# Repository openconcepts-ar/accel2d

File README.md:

# Hardware accelerated graphics (2D GPU) - graphics server system

## Introduction

This project aims to provide a graphics server system based on hardware accelerated graphics, and a easy way to develop the graphics primitives. The accelerated versions runs faster using the exact same C code as the software version by automatic translation (*transpiling*) to Verilog code.

As an example, let's see how to use and develop drawing privimites for solid rectangles and ellipses.

Ellipse case (see [ellipse_fill32.cc](./ellipse_fill32.cc) file):

    MODULE ellipse_fill32(
      bus_master(bus),
      const uint16&	x0,
      const uint16&	x1,
      const uint16&	y0,
      const uint16&	y1,
      const uint32&	rgba, //color
      const uint32& base, //pixel offset
      const int16& xstride, //normally 1, but can run backwards
      const int16& ystride //bytes to skip for next line (usually the framebuffer width * 4 bytes)
      )

The `bus` argument is automatically handled both in software and in hardware by privided macros.  
The rectangle primitive follows the same function signature.

## Software implementation

You can directly call the function using compilation with a normal C compiler:

    ellipse_fill32(BUSMASTER_ARG, x0, x1, y0, y1, rgba, base, xstride, ystride);

The BUSMASTER_ARG macro is an automatic argument, defined on a provided header file.
It's useful for the implementation of the hardware accelerated primitive, as explained in the next section.

The following image is produced by the simulator by calling 1000 times to the software implementation of the primitives,  using random coordinates:

</img>

## Hardware implementation

To target hardware implementation on a FPGA, a [Verilog](./ellipse_fill32.v) file is automatically generated from from the [corresponding C file](./ellipse_fill32.cc) having the drawing primitive algorithm, by using the following external tools: [CflexHDL](https://github.com/suarezvictor/CflexHDL) and the [Silice](https://github.com/sylefeb/Silice) transpilers (see [Makefile.common](./Makefile.common) target "c2v" for the invocation command details). Since this project aims to be transpiler-agnostic, the [PipelineC](https://github.com/JulianKemmerer/PipelineC) transpiler is planned for a future version.

See a portion of the generated Verilog code, where part of the C expressions and interactions with the memory bus can be readily appreciated:

    4: begin
        if (_q_x<_q_rw) begin
            _t_xx = _q_x*_q_x;
            _t_xh = (_t_xx)*(_q_hh);
            if (_t_xh+_q_yw<_q_wh) begin
                _d_bus_dat_w = in_rgba;
                _d_bus_we = 1;
                _d_bus_stb = 1;
                _d_bus_cyc = 1;
                if (!((_d_bus_stb&&_d_bus_we)&&!(_d_bus_stb&&in_bus_ack&&_d_bus_we))) begin
                    _d_bus_stb = 0;
                    _d_bus_adr = (_q_bus_adr+(in_xstride));
                    _d_x = _q_x+1;
                end
            end else begin
                _d_bus_adr = (_q_bus_adr+(in_xstride));
                _d_x = _q_x+1;
            end
            _d__idx_fsm0 = 4;
        end else begin
            _d__idx_fsm0 = 5;
        end
    end

After generating a System On Chip (SoC) for the target FPGA using the [LiteX](https://github.com/enjoy-digital/litex) framework and a [provided](./digilent_arty.py) script, that includes the generated verilog files, the accelerator can be called as follows:

    regs->x0 = x0;
    regs->x1 = x1;
    regs->y0 = y0;
    regs->y1 = y1;
    regs->base = VIDEO_FRAMEBUFFER_BASE + y0*FRAME_PITCH + x0*sizeof(rgba);
    regs->xstride = SDRAM_BUS_BITS/8;
    regs->ystride = FRAME_PITCH;
    regs->rgba = rgba;

    regs->run = 1; //start
    while(!regs->done); //wait until done

As seen, you first set memory mapped registers with the desired values, then you start the core, then wait until the `done` flag is set.

Each accelerator core gets mapped starting at a fixed address (default 0x80000000 for the first accelerator, 0x80000800 for the second and so on, as provided by the correspoding macros). A C structure with the layout of registers is conveniently provided too (each register is 32-bit aligned, even if smaller).

The resulting execution in hardware is as follows:

</img>

## Testing equivalence of software and hardware

You can visually appreciate that both images seems like the same, but how we can be sure the generated Verilog behaves the same as the software implementation? The solution is to use the accelerated implementations and also call the compiled software implementation in the same SoC, then we can compare if results are the same. The [test program](./drawing_test.c) does specifically that, reporting how many pixels are in error, if any:

You can see that the accelerator is about **3X faster**, while it also frees the CPU for other tasks.

In case of any discrepance, non-matching pixels are marked in red (this was generated by inducing a coordinate error in the software implementation) and the amount of pixels in error is reported.

Console output would be in this case:  
  
    Pixel errors: 320 (screen should have no red pixels)

    ==========================================
    *** TESTS FAILED ***
    ==========================================

## Prototype application and simulator

The acceleration is readily appreciated on the following [video](https://peertube.io/w/8ds2de9pjt3c6C22reAnZc), where the software implementation is run prior to the hardware one. After that, a *clock demo* application is shown, using a combination of drawn rectangles and ellipses.

</img>

The [code](./drawing_test.c) for that demo application can be compiled with the main [simulator](./sim_linux.c) code on the host machine (e.g. Linux) to see results on the simulator window. This eases testing while in development since the program compiles in few seconds, then it can be run on the hardware platform to check if producing the same results. In the provided video, you can see that the hardware matches the simulator.

## Accelerator performance

Accelerator cores gets directly connected to the dynamic RAM of the respective boards (acting similarly as a DMA), and using caching to achieve access at high speed. That way, the accelerated cores are about 7X faster than when running in software, as the current tests reports (line drawing core on a ECP5 device):

</img>

    Start software rendering
    elapsed 9057225 us, ops/s: 828153 (2 FPS @640x480)
    Switch to hardware rendering
    elapsed 1229585 us, ops/s: 6100246 (19 FPS @640x480)
    Just waiting a bit to evaluate image...
    Pixel errors: 0 (screen should have no red pixels)
    
    ==========================================
    TESTS PASSED
    ==========================================

The following [video](https://peertube.io/w/5h4g7QTLPuHQ6vtsUj8WzR) shows the corresponding images on the display (first the software renderer, then the accelerated renderer).

## Supported boards

Curently the project supports the following boards:  
[Lambdaconcept ECPIX-5](https://shop.lambdaconcept.com/home/46-ecpix-5.html) with a Lattice ECP5 device. It currently utilices an open source toolchain for building the bitstream. The board name used in the project is *lambdaconcept_ecpix5*.

[Digilent Arty A7-35T](https://digilent.com/reference/programmable-logic/arty-a7/) with an AMD Artix7 device. The board name used in the project is *digileny_arty*.

# Build instructions

Just run:

    make BOARD=lambdaconcept_ecpix5 run upload

Where the target *run* runs the simulator, and the *upload* target makes the bitstream and uploads it to the FPGA board.

# Micropython support, with graphics
The FPGA board is now capable of running a graphics-enabled micropython port, capable of controlling a PC monitor.
Up to 8 bit per color channel are supported.
  
Example: [accel_basic.py](./demos/micropython/accel_basic.py)  
  
</img>

## Build & run instructions for micropython:
Generate and upload the bitstream (use your own serial port location if different):

    make BOARD=digilent_arty digilent_arty SERIAL_PORT=/dev/ttyUSB1
    cd micropython/ports/litex
    make
    litex_term.py --kernel build/firmware.bin /dev/ttyUSB1
    cd -
    openFPGALoader -b arty build/digilent_arty/gateware/digilent_arty.bit

Then the .py file can be uploaded using the standard `mpremote` command:

    mpremote connect /dev/ttyUSB1 run demos/micropython/accel_basic.py

This generates the following picture:  
  
</img>

To run the clock demo, [accel_clock.py](./demos/micropython/accel_clock.py)  (in same folder)

## Micropython support on the CPU board
  
The same repository used for the port of micropython to the FPGA platform was used to target the project's CPU board (F133A SoC by Allwinner Tech)

Supported features are:  
  * REPL (Python prompt) over UART  
  * Minimal umachine support  
  * Time functions (except RTC)  
  * Video Framebuffer
  * Dynamic memory allocation (using the internal DDR2 RAM)

The repository of the extended micropython is linked as a git submodule on the main repo (see [micropython@51dfc37b30](https://notabug.org/suarezvictor/gpu2d) at the project's main repo). The sub repository directs to the micropython [repo](https://github.com/suarezvictor/micropython/tree/gpu2d).

The source for the f133 port are under the following [folder](https://github.com/suarezvictor/micropython/tree/gpu2d/ports/f133)
  
A basic example to test micropython on the CPU is to use the REPL mode:
  
</img>

Under the f133 folder, there's a micropython script that shows how to access the video framebuffer: [test/test_video.py](https://github.com/suarezvictor/micropython/blob/gpu2d/ports/f133/test/test_video.py)
  
</img>

Execution of this produced the following result:
  
</img>

Note the compatibility of the micropython code with the one for the [FPGA platform](https://github.com/suarezvictor/micropython/blob/gpu2d/ports/litex/test/test_video.py).

## Build instructions:  
```
cd ports/f133
make
```
The `make` command will build the firmware and upload it to the board. To upload new firmware, you have to first push the reset button.

# New CPU-based board
A brand-new board was designed using a graphics-capable CPU:

</img>

It's capable of running the [clock demo](./target-cpu/drawing_test.c), using the graphics primitives [ellipse](./ellipse_fill32.cc) and [rectangle fill](./rectangle_fill32.cc)

This produces the following image:  
</img>

## Build instructions:  
```
   cd target-cpu/f133-bare/
   make
```

The `make` command will build the firmware and upload it to the board. To upload new firmware, you have to first push the reset button.

This milestone is **conclusive proof** that this framework is capable running the drawing primitives as software or hardware, since the same code runs on the CPU as software and in the FPGA as a hardware core, producing matching visual results.

The same port of micropython to the FPGA platform was used to target the project's CPU board (F133A SoC by Allwinner Tech)

# Serial communications

The CPU board is capable of communication using serial ports, they're typically used to control the board externally and to get debug messages.

See an example of boot mesages outputted from the default debug port (UART0):
  
</img>

See below an example interaction with micropython using the second port (UART1), accesible in the board at the 6-pin header (bottom left).
  
</img>

This is achieved in software by calling a initialization function `uart_probe(UART_COMM)` to enable the second port. See [main.c](target-cpu/f133-bare/main.c) for a example usage and [driver_uart.c](target-cpu/f133-bare/driver_uart.c) for the implementation.

## I2C
An I2C driver was added to the micropython port for the CPU board. It can access display information provided by PC monitors and determine available resolutions.

It works by configuring I/O pins for open-drain behaviour, thus electrically compatible with the I2C standard.
See [mphalport.h](https://github.com/suarezvictor/micropython/blob/1be3d4751f3e6832b87b66c13be2fca8f1f1078a/ports/f133/mphalport.h#L64) for implementation details.

The micropython script to run is: [i2c_vga_ddc.py](demos/micropython/i2c_vga_ddc.py), which obtains the following information:
  
</img>

The script can be run from the Linux console with the `mpremote` command:
```
mpremote connect /dev/ttyUSB0 run demos/micropython/i2c_vga_ddc.py
```

The wiring can be done using the [I/O board](hardware/IO_board) using a 40-pin FPC cable and direct wiring to the VGA connector as shown:   
</img>

# Software JPEG image decompression

A new function to decompress JPEG file was implemented, it's based on the C model of a [Verilog decompressor](https://github.com/ultraembedded/core_jpeg), so in that form it's useful to test things in sofware before moving it to hardware. The original code was changed to avoid dynamic memory allocations thus easier to run in the bare metal environment, see [target-cpu/f133-bare](target-cpu/f133-bare) for sources.

A JPEG file is embedded in the firmware image by means of a direct include of the raw file data (.incbin directive in the [rawdata.S](target-cpu/f133-bare/rawdata.S) assembler source)

The example image size is 33.8KB when compressed and 921.6 KB when decompressed (27:1 ratio). Software decompresion takes 195ms (5FPS) expected to reach 30FPS with the planned video decoder accelerator (Verilog).

Working example on the bare metal enviroment:
  
</img>

The decompression algorithm is in the [c_model_jpeg_test.cpp](target-cpu/f133-bare/c_model_jpeg_test.cpp) source.

# About [NLnet](http://nlnet.nl) Foundation

</img>

This [project](https://nlnet.nl/project/Hardware-2D) is funded through the NGI0 Entrust Fund, a fund established by NLnet with financial support from the European Commission's Next Generation Internet programme, under the aegis of DG Communications Networks, Content and Technology under grant agreement No 101069594.

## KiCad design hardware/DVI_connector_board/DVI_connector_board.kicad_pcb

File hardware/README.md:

# HARDWARE (boards)

Here are the design files for the current boards of this project:  

Processing boards:  
  * [CPU board](#cpu-board-design) [_viewer_](https://kicanvas.org/?repo=https%3A%2F%2Fgithub.com%2Fopenconcepts-ar%2Faccel2d%2Ftree%2Fpcbfixes1%2Fhardware%2FCPU_board)  
  * [ECP5 FPGA board](#ECP5-fpga-board-design) [_viewer_](https://kicanvas.org/?repo=https%3A%2F%2Fgithub.com%2Fopenconcepts-ar%2Faccel2d%2Ftree%2Fpcbfixes1%2Fhardware%2FFPGA_board)  
  * [Spartan-6 FPGA board](#spartan-6-fpga-board) [_viewer_](https://kicanvas.org/?repo=https%3A%2F%2Fgithub.com%2Fopenconcepts-ar%2Faccel2d%2Ftree%2Fpcbfixes1%2Fhardware%2FSpartan6_board)  

Adapter boards:  
  * [eDP adapter board](#edp-adapter-design) [_viewer_](https://kicanvas.org/?repo=https%3A%2F%2Fgithub.com%2Fopenconcepts-ar%2Faccel2d%2Ftree%2Fpcbfixes1%2Fhardware%2FeDP_adapter)  
  * [eDP adapter board, alternate IC version](#edp-adapter-design) [_viewer_](https://kicanvas.org/?repo=https%3A%2F%2Fgithub.com%2Fopenconcepts-ar%2Faccel2d%2Ftree%2Fpcbfixes1%2Fhardware%2FeDP_adapter%2Fedp_adapterITE)  
  * [VGA adapter](#vga-adapter-board-design) & connector [_viewer_](https://kicanvas.org/?repo=https%3A%2F%2Fgithub.com%2Fopenconcepts-ar%2Faccel2d%2Ftree%2Fpcbfixes1%2Fhardware%2FVGA_adapter)  
  * [LVDS adapters](#lvds-adapter-board-design) single and dual channel [_viewer_](https://kicanvas.org/?repo=https%3A%2F%2Fgithub.com%2Fopenconcepts-ar%2Faccel2d%2Ftree%2Fpcbfixes1%2Fhardware%2FLVDS_adapter)  
  * [DVI adapter](#dvi-adapter-board-design) & connector [_viewer_](https://kicanvas.org/?repo=https%3A%2F%2Fgithub.com%2Fopenconcepts-ar%2Faccel2d%2Ftree%2Fpcbfixes1%2Fhardware%2FDVI_adapter)  
  * [DVI passive adapter](#dvi-passive-adapter-board-design) [_viewer_](https://kicanvas.org/?repo=https%3A%2F%2Fgithub.com%2Fopenconcepts-ar%2Faccel2d%2Ftree%2Fpcbfixes1%2Fhardware%2FDVI_connector_board)  
  * [USB to I2C bridge](#usb-to-i2c-bridge) [_viewer_ NOTE: select USBHOST project](https://kicanvas.org/?repo=https%3A%2F%2Fgithub.com%2Fopenconcepts-ar%2Faccel2d%2Ftree%2Fpcbfixes1%2Fhardware%2FTouch_splitter)   

Debugging boards:  
  * [DVI receiver](#dvi-receiver-board) [_viewer_](https://kicanvas.org/?repo=https%3A%2F%2Fgithub.com%2Fopenconcepts-ar%2Faccel2d%2Ftree%2Fpcbfixes1%2Fhardware%2FDVI_receiver)  
  * [Touch splitter](#touch-splitter-board) [_viewer_](https://kicanvas.org/?repo=https%3A%2F%2Fgithub.com%2Fopenconcepts-ar%2Faccel2d%2Ftree%2Fpcbfixes1%2Fhardware%2FTouch_splitter)  
  * [I/O board](#io-board-design) [_viewer_](https://kicanvas.org/?repo=https%3A%2F%2Fgithub.com%2Fopenconcepts-ar%2Faccel2d%2Ftree%2Fpcbfixes1%2Fhardware%2FIO_board)  

## CPU board design
A second, smaller version of the CPU board was designed, based again on the Allwinner F133A CPU  
  
It features:  
  * C906 64-bit RISC-V CPU @1GHz (22nm manufacturing process)  
  * Integrated 64MB DDR2 RAM  
  * Small size, breadboard compatible  
  * SD card socket to store media assets  
  * 2 USB-C connectors with Host and OTG (Host/Device) functions, respectively  
  * Video output connector  
  * Headers for serial I/O and power  
  * Reset and boot buttons
  * JTAG debugging using "pogo-pins"  

The design is done with the open-source EDA tool [Kicad](https://kicad.org), the source files are [here](./CPU_board)  
The board is 4 layer, based on the [Yuzuki design](https://bbs.aw-ol.com/topic/922/%E5%BC%80%E6%BA%90-yuzukinezha-d1s-%E6%A0%B8%E5%BF%83%E6%9D%BF-mini-pice-%E6%A0%B8%E5%BF%83%E6%9D%BF/3), with **CERN open-source hardware** license.
  
PDF schematics are [here](./CPU_board/CPU_board_schematics.pdf).  

## ECP5 FPGA board design

The ECP5 FPGA board is capable of instancing a RISC-V CPU along with the hardware accelerators desiged in C and automatically translated to Verilog.
Not only the board has the same layout as the CPU board but the drawing primitives use the same C sources, as one of the main objectives of the project.

Features are:  
  * Lattice ECP5 FPGA device, supporting 12F, 25F, 45F and 85F sizes in 285 ball BGA package  
  * DDR3L RAM of up to 1Gbit with impedance controlled tracks  
  * Small size, breadboard compatible  
  * SD card socket to store media assets  
  * 2 USB-C connectors with Host and Device functions, respectively  
  * Video output connector  
  * Headers for serial I/O  
  * Reset button (also for bitstream loading)
  * JTAG debugging using "pogo-pins"  

The design is done with the open-source EDA tool [Kicad](https://kicad.org), the source files are [here](./FPGA_board)  
The board is 6 layer, based on the [OrangeCrab board r0.1](https://orangecrab-fpga.github.io/orangecrab-hardware/docs/r0.1/), with **CERN open-source hardware** license.
  
PDF schematics are [here](./FPGA_board/FPGA_board_schematics.pdf).  

*NOTE: FPGA chip is not shown on the 3D rendering for lack of a 3D model for the part*

## Spartan-6 FPGA board

The Spartan-6 FPGA board is a lower cost version FPGA board. It includes a DDR3 memory and a RP2040 MCU. I/O includes a flash memory connector, USB-C device port, a 20-pin FPC connector for DVI (TDMS) signals, and a SWD debug header.  

The design is done with the open-source EDA tool [Kicad](https://kicad.org), the source files are [here](./Spartan6_board)  
The board is 6 layer, based on the [Modos Glider Lite](https://github.com/Modos-Labs/Glider/tree/df32bba2b8f32c97958a599ba021d12184ffeada/pcb/mainboard_lite), with **CERN open-source hardware** license.
  
PDF schematics are [here](./Spartan6_board/pcb.pdf).  

## eDP adapter design

This adapter is capable of converting <s>digital RGB parallel signals NOTE: lack of docs prevents this, see eDP_adapter/EDP.md</s> LVDS signals to eDP protocol for direct driving of laptop replacement displays using a standard FPC cable. The converter IC is NCS8801S from [NewCoSemi](https://www.newcosemi.com/), or IT6251 from [ITE](https://www.ite.com.tw/en) as an alternative. Note they are 4-layer design for better signal integrity, as required by the high-speed differential LVDS inputs and eDP outputs.

The design source files are [here](./eDP_adapter).  
PDF schematics for the adapter are [here](./eDP_adapter/eDP_adapter.pdf).  

**Alternate version**:  

The design source files are [here](./eDP_adapter).  

Thiese designs are relased under a **CERN open-source hardware** license, using the the open-source EDA tool [Kicad](https://kicad.org)

## VGA adapter board design

This adapter is capable of converting digital RGB parallel signals to VGA-compatible analog values, using a simple R-2R DAC. The adapter board outputs the VGA signals to a 15-pin flat cable, to be connected 1:1 to a connector board that has the D-sub (15-pin) starndard VGA connector.

The design is done with the open-source EDA tool [Kicad](https://kicad.org), the source files are [here](./VGA_adapter) (adapter) and [here](./VGA_connector_board) (connector)  
PDF schematics for the adapter are [here](./VGA_adapter/VGA_adapter_schematics.pdf).  
  
This design is relased under a **CERN open-source hardware** license.

## LVDS adapter board design

This board connects 4 or 8 pairs of differential signals to a LCD using LVDS signalling (of the kind commonly used for older laptops displays), to directly drive them (single and dual channel). It also connect signals that can identify the display model and resolution using I2C.

Features:  
  * 40-pin FPC cable connector  
  * Protection diodes  
  * I2C connection for display [EDID](https://en.wikipedia.org/wiki/Extended_Display_Identification_Data) reading  
  * External header for powering the backlight  

The design is done with the open-source EDA tool [Kicad](https://kicad.org), the source files are [here](./LVDS_adapter), licensed under a **CERN open-source hardware** license.  
  
PDF schematics for the adapter are [here](./LVDS_adapter/LVDS_adapter_schematics.pdf) (single channel) and [here](./LVDS_adapter/LVDS_adapter_2ch.pdf) (dual channel).  

**Dual channel**

**Single channel**

**8-bit dual channel**

This boards outputs a standard 2x15 2mm pitch LVDS connector on the side, supporting 1 or 2 channel, 6- or 8-bit versions. It adds a 6-pin I2C connector on the back for touch signals.  

## DVI adapter board design

This board converts parallel RGB signals to digital video signals in the DVI format, as accepted by the majority of current PC monitors and TVs.

Features:  
  * 20-pin FPC cable connector, compatible with standard [FPV Ribbon cables](https://duckduckgo.com/?hps=1&q=FPV+HDMI+Ribbon+Cable) for connection to displays  
  * Protection diodes  
  * I2C connection for display [EDID](https://en.wikipedia.org/wiki/Extended_Display_Identification_Data) reading  
  * Solder jumpers for the main IC configuration  

The design is done with the open-source EDA tool [Kicad](https://kicad.org), the source files are [here](./DVI_adapter) (adapter) and [here](./DVI_connector_board) (connector), licensed under a **CERN open-source hardware** license.  
  
PDF schematics for the adapter are [here](./DVI_adapter/DVI_adapter_schematics.pdf).  

**Connector board**
  
This was fixed for better signal integrity using a G-S-S-G scheme for the differential signals, using a pinout that is common in off-the-shelf extension adapters.   

## DVI passive adapter board design

This is for outputting LVDS signals from a FPGA using AC-coupling to drive a TDMS receiver, using a standard connector for carring DVI video signals.
It includes a level adapter to convert 5V I2C to 3.3V (VIO).

The design is done with the open-source EDA tool [Kicad](https://kicad.org), the source files are [here](./LVDS_DVI_adapter), licensed under a **CERN open-source hardware** license.  
  
PDF schematics for the adapter are [here](./LVDS_DVI_adapter/LVDS_DVI_adapter.pdf).  

## DVI receiver board

This board converts DVI (TDMS) signals to parallel RGB signals + H/V sync. It is based on the TFP401 chip from TI.

The design is done with the open-source EDA tool [Kicad](https://kicad.org), the source files are [here](./DVI_adapter) (adapter) and [here](./DVI_connector_board) (connector), licensed under a **CERN open-source hardware** license.  
  
PDF schematics for the adapter are [here](./DVI_adapter/DVI_adapter_schematics.pdf).  

## Touch splitter board

The touch splitter board allows to split the signals from a 40-pin eDP display woth on-cell touch, separating the 30-pin eDP signals and the USB touch signals. It supports powering the touch model with 5V or 3.3V.

The design is done with the open-source EDA tool [Kicad](https://kicad.org), the source files are [here](./Touch_splitter). 

## USB to I2C Bridge
This board is a 40-pin extended eDP with touch to 30-pin with bridged I2C. It is similar top the Touch splitter board, but "active": instead of passively exposing the USB signals to an external connector, it routes them to a MCU.
  
The board uses a RP2354 as the MCU wich supports USB full-speeed host (unsing the USB signals on the connector with the additional 10 pins) and outputs I2C data over a usual 30-pin eDP connector. It uses "OEM reserved" pins to route the I2C signals and the interrupt pin. This is received by the eDP adapter which supports touch-enabled display reusing it's 30-pin output FPC connector, being still compatible with non-touch enabled 30-pin displays.

The design is done with the open-source EDA tool [Kicad](https://kicad.org), the source files are [here](./Touch_splitter), see `eDP_touch_adapter_USBHOST.kicad_*` files. 

## I/O board design

The I/O board adapter allows to externally access the video signals (present on the 2x15 connectors) for other purposes like general purpose I/O pins and debug.

It uses a 40-pin FPC connector and cable that allows to break out the signals, in a more manageable way like using common wires as the ones usually for bread boards.

Also, it includes two 31-pin FPC connectors at 0.3mm pitch for replacing the Hirose connectors with FPC or FFCs.
All the wiring are directo connections to the video connectors. A header to acces the touchscreen signal is also provided.

The design is done with the open-source EDA tool [Kicad](https://kicad.org), the source files are [here](./IO_board), licensed under a **CERN open-source hardware** license.  

# Latest updates

See most relevant [commit](https://github.com/openconcepts-ar/accel2d/commit/21333764fecb12ceccd276d67593bb1683f1b8bd).  

  * Added [eDP adapter board](#edp-adapter-design), alternate version
  * Added [USB to I2C bridge](#usb-to-i2c-bridge)
  * Added [LVDS adapters, 8-bit version dual channel](#lvds-adapter-board-design)
  * Updated [eDP adapter board](#edp-adapter-design) to 4 layers
  * Added [Spartan-6 FPGA board](#spartan-6-fpga-board)
  * Added [DVI receiver board](#dvi-receiver-board)
  * Added [Touch splitter board](#touch-splitter-board)
  * [ECP5 FPGA board](#ECP5-fpga-board-design): Added support to larger 85F version, add Replacement of 2.5V source (DC-DC or LDO option), USB connectors swap (note location matches the CPU board), thermal fix (replaced flash of wrong voltage, now larger to accomodate 85F devices, and added both LDO and higher capacity DC-DC for the 2.5V rail, selectable via solder pad)
  * [DVI passive adapter](#dvi-passive-adapter-board-design): make PCB significantly shorter
  * [DVI connector](#dvi-adapter-board-design) board: fixed DVI connector (previously mini version of 0.4mm pitch, now 0.5mm like the standard version)
  * [LVDS adapters](#lvds-adapter-board-design)  (2ch): Fixed bug of bad GND plane fill, which produced massive shorts
  * [CPU board](#cpu-board-design): Add impedance control to differential tracks, corrected size of vias for , bootsel fix, dim led
  * DRC checks for all boards, with DFM checks for 4 and 6 layers boards

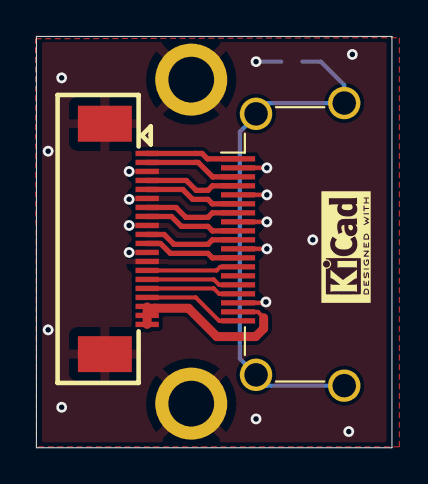
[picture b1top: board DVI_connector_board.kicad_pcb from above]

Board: 2 copper layers, 19.8 x 22.9 mm, 5 parts (1 on the bottom side), 15 nets.

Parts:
J1: FPC Cable connector 1x20; XFCN_F0501-B-20-20T-R
J2: HDMI_A; HDMI_A_Amphenol_10029449-x01xLF_Horizontal
JP1: JMP_DKEN; SolderJumper-2_Open_RoundedPad_2.254x0.95mm
MH1, MH2: (no value)

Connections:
/CK+: J1.10, J2.10 (CK+)
/CK-: J1.11, J2.12 (CK-)
/D0+: J1.7, J2.7 (D0+)
/D0-: J1.8, J2.9 (D0-)
/D1+: J1.4, J2.4 (D1+)
/D1-: J1.5, J2.6 (D1-)
/D2+: J1.1, J2.1 (D2+)
/D2-: J1.2, J2.3 (D2-)
GND: J1.0, J1.3, J1.6, J1.9, J1.12, J1.13, J2.2 (D2S), J2.5 (D1S), J2.8 (D0S), J2.11 (CKS), J2.17 (GND), JP1.1 (A), MH1.18, MH2.18
unnamed: J1.18, J1.19, J1.20, J2.18 (+5V)
unnamed: J1.14, J2.13 (CEC)
unnamed: J1.17, J2.19 (HPD)
unnamed: J1.15, J2.15 (SCL)
unnamed: J1.16, J2.16 (SDA)
unnamed: J2.SH, JP1.2 (B)

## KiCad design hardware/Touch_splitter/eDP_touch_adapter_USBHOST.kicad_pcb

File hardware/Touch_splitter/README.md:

# USB Touch adapter eDP USBHOST v0.1

The current design, based on the active oscillator YE12MUBCE2O to avoid crystals and capacitors -at just 2.0x1.6mm-proved to be good, saving board space.  
The polarized inductor is as small works too
The board needs external 3.3V power (note that a display controller CAN CUT POWER if a display is not detected or for standby). This may imply that  the touch sensor may take power from the display power or independently (so it is possible that the touch panel works without powering the image display).  

## Build and firmware loading
Build all projects, then:
```
cd examples
mkdir -p build && cd build
export PICO_SDK_PATH=/path/to/pico-sdk/ #point to your location
cmake -DPICO_BOARD=pico2 .. #or BOARD=pico for RP2040
make -j
```
Now upload the firmware:
```
cp host_hid_to_uart/host_hid_to_uart.uf2 /media/$USER/RP2350 #or where the USB MSC gets mounted
```
TX pin is GPIO20 (TP2), RX is GPIO21 (TP3), INT is GPIO19 (TP4). The panel under test is specified to receive 5V the supply but it worked at 3.3V.  

## Board testing

Example receiving the multitouch data on a PC:
```
13292ms: Magic 03 EVENT type 02, addr 01, instance 00, [2a94:5009] payload len 0040:
report 0, block 0, type TipSwitch (19), id 66, offset 8, size 1, value 1 (-1)
report 0, block 0, type ContactId (20), id 81, offset 16, size 8, value 0 (0)
report 0, block 0, type X (6), id 48, offset 24, size 16, value 126 (126)
report 0, block 0, type Y (7), id 49, offset 40, size 16, value 152 (152)
```

## Test results

Tested at HD and FHD.
No signal integrity problems or issues of other kind found.
The non-standard pin 24 and 25 on the 30-pin eDP connector dont interfere with video signals either.

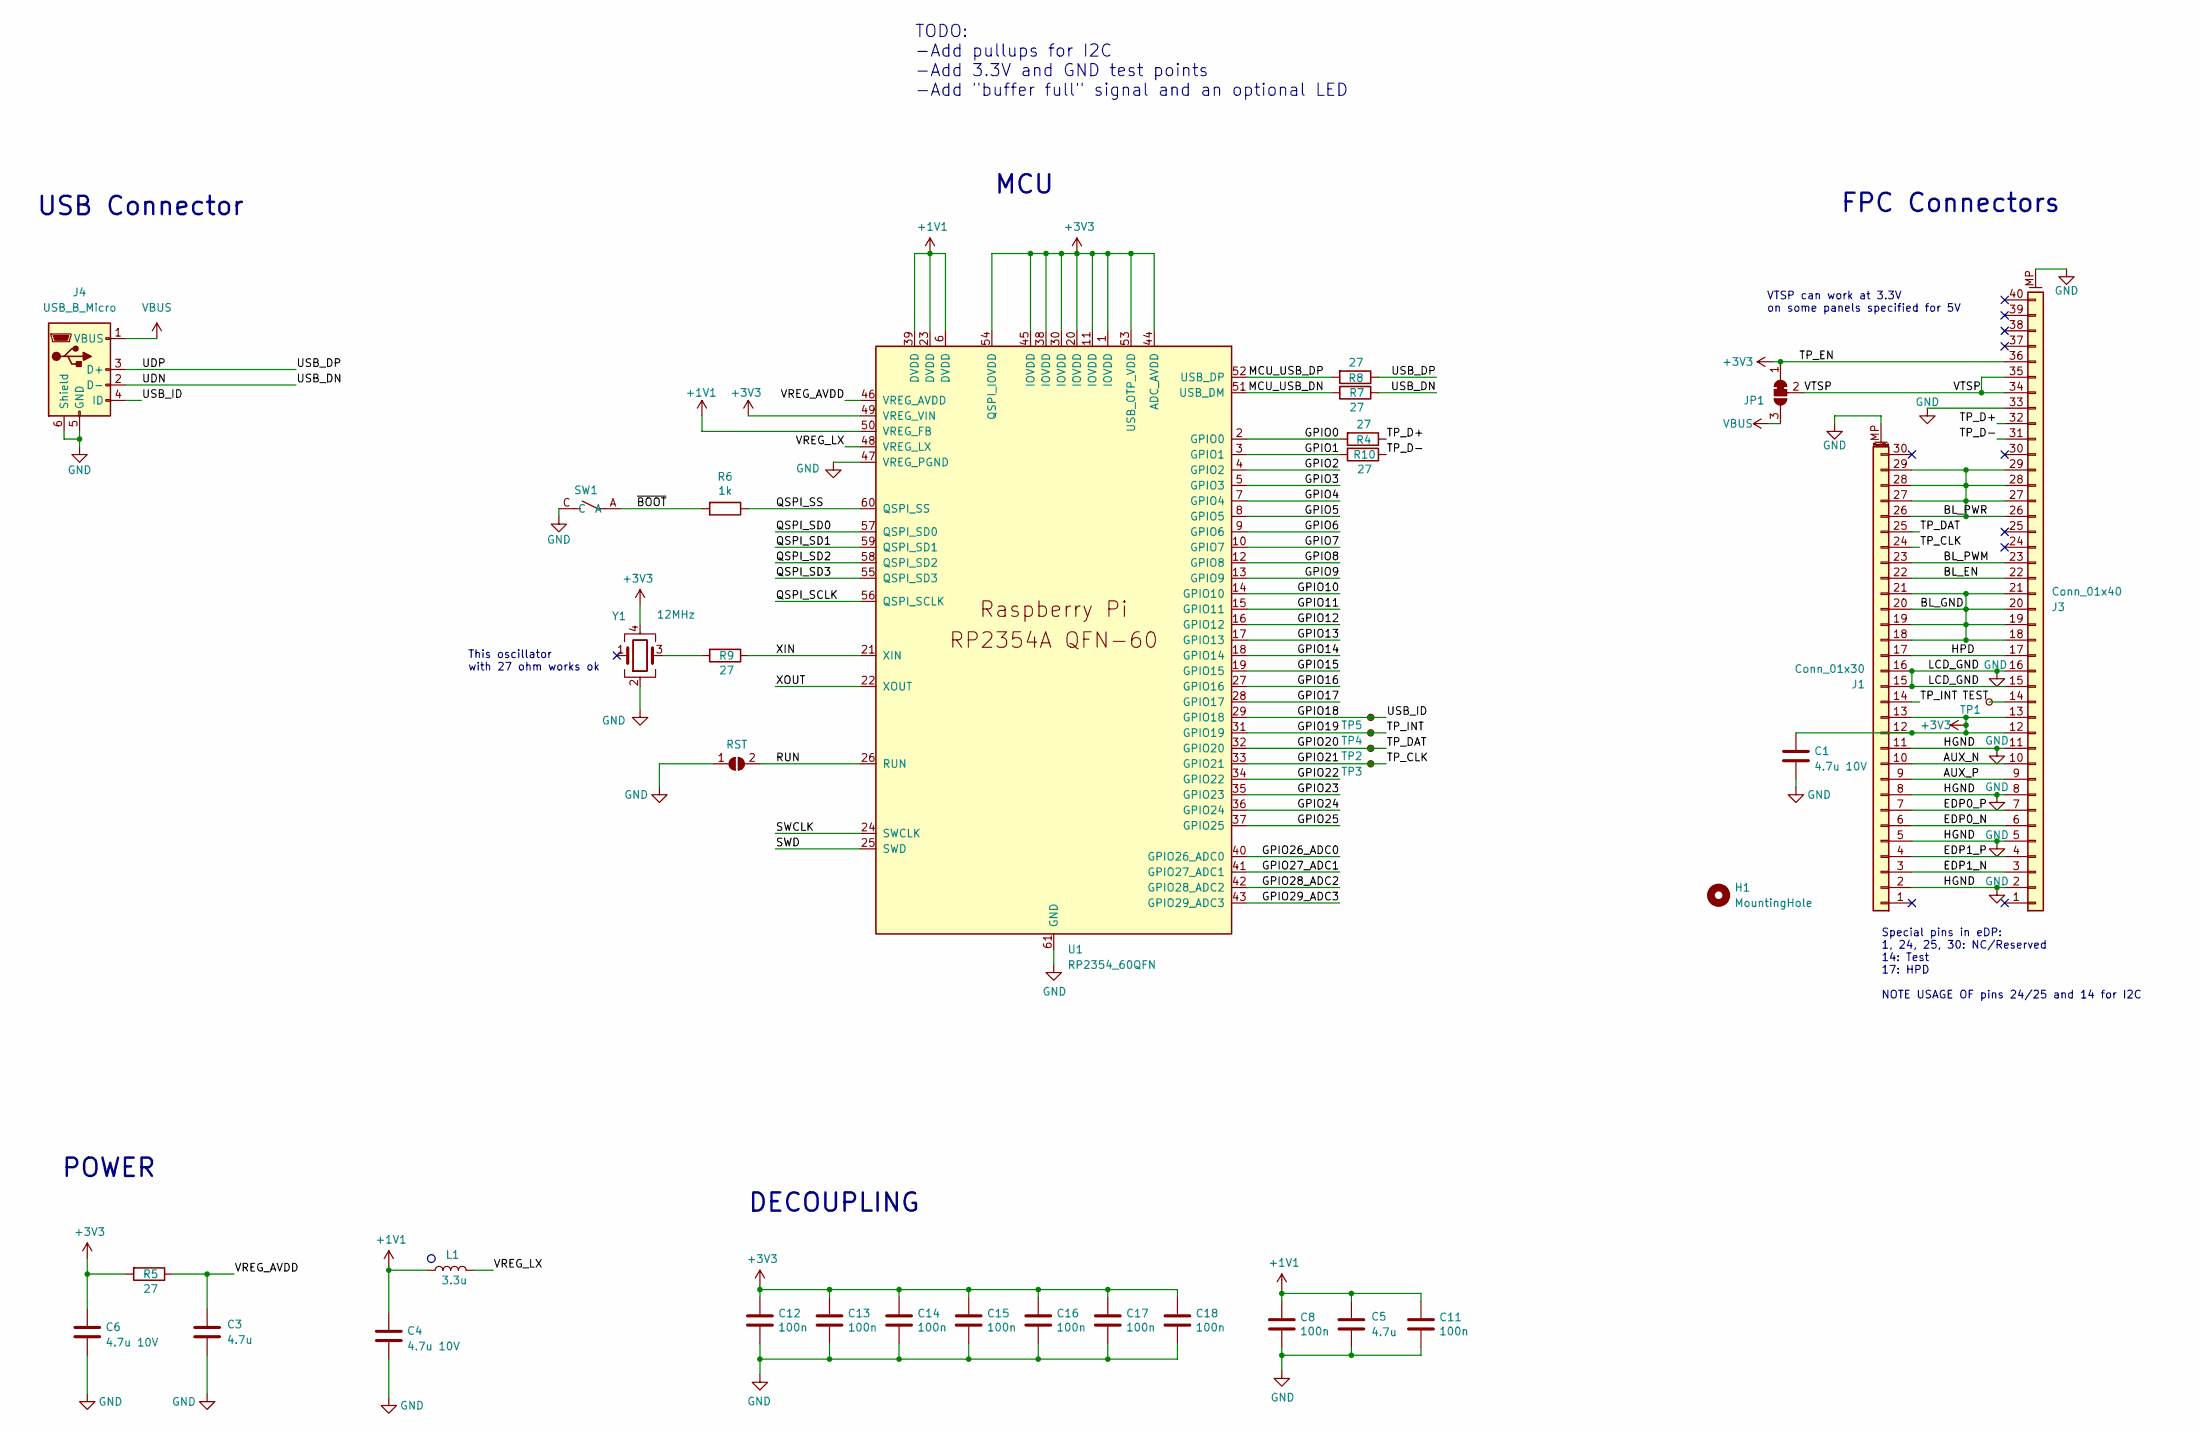
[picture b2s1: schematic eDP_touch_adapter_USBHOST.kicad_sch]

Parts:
C1, C4, C6: 4.7u 10V; C_0402_1005Metric_small_pads; MPN CL05A475KP5NRNC
C3, C5: 4.7u; C_0402_1005Metric_small_pads; MPN CL05A475KP5NRNC
C8, C11, C12, C13, C14, C15, C16, C17, C18: 100n; C_0402_1005Metric
H1: MountingHole; MountingHole_2.2mm_M2
J1: Conn_01x30; FPC-SMD_30P-P0.50_FPC-0.5FX-30PWBH15; MPN FPC-0.5FX-30PWBH15; LCSC Part Number C3446034
J3: Conn_01x40; FPC-SMD_XUNPU_FPC-0.5FX-40PWBH15; MPN FPC-0.5FX-40PWBH15; LCSC Part Number C3446035
J4: USB_B_Micro; MICRO-USB-SMD_MICRO-XNJ-ZB; MPN MICRO XNJ ZB; LCSC Part Number C668587
JP1: SolderJumper_3_Bridged12; SolderJumper-3_P1.3mm_Bridged12_RoundedPad1.0x1.5mm
JP2: RST; SolderJumper-2_P1.3mm_Open_RoundedPad1.0x1.5mm
L1: 3.3u; L_pol_2016; MPN AOTA-B201610S3R3-101-T; LCSC Part Number C42411119
R4, R5, R7, R8, R9, R10: 27; R_0402_1005Metric
R6: 1k; R_0402_1005Metric
SW1: SW_Push; SW-SMD_4P-L2.5-W1.6-LS2.9_STI-055A12AX; MPN GT-TC194A-H0055-L1; LCSC Part Number C41398745
TP1, TP2, TP3, TP4, TP5: TestPoint_Small; TestPoint_Pad_D2.0mm
U1: RP2354_60QFN; RP2350-QFN-60-1EP_7x7_P0.4mm_EP3.4x3.4mm_ThermalVias; MPN RP2354A; LCSC Part Number C41378174
Y1: 12MHz; OSC-SMD_4P-L2.0-W1.6-BL_8NE; MPN YE12MUBCE2O; LCSC Part Number C54307921

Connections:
+1V1: C4.1, C5.1, C8.1, C11.1, L1.1, U1.6 (DVDD), U1.23 (DVDD), U1.39 (DVDD), U1.50 (VREG_FB)
+3V3: C1.1, C6.1, C12.1, C13.1, C14.1, C15.1, C16.1, C17.1, C18.1, J1.12, J1.13, J3.12, J3.13, J3.36, JP1.1 (A), R5.2, U1.1 (IOVDD), U1.11 (IOVDD), U1.20 (IOVDD), U1.30 (IOVDD), U1.38 (IOVDD), U1.44 (ADC_AVDD), U1.45 (IOVDD), U1.49 (VREG_VIN), U1.53 (USB_OTP_VDD), U1.54 (QSPI_IOVDD), Y1.4
/AUX_N: J1.10, J3.10
/AUX_P: J1.9, J3.9
/BL_EN: J1.22, J3.22
/BL_GND: J1.18, J1.19, J1.20, J1.21, J3.18, J3.19, J3.20, J3.21
/BL_PWM: J1.23, J3.23
/BL_PWR: J1.26, J1.27, J1.28, J1.29, J3.26, J3.27, J3.28, J3.29
/EDP0_N: J1.6, J3.6
/EDP0_P: J1.7, J3.7
/EDP1_N: J1.3, J3.3
/EDP1_P: J1.4, J3.4
/GPIO0: R4.2, U1.2 (GPIO0)
/GPIO1: R10.2, U1.3 (GPIO1)
/GPIO2: U1.4 (GPIO2)
/GPIO3: U1.5 (GPIO3)
/GPIO4: U1.7 (GPIO4)
/GPIO5: U1.8 (GPIO5)
/GPIO6: U1.9 (GPIO6)
/GPIO7: U1.10 (GPIO7)
/GPIO8: U1.12 (GPIO8)
/GPIO9: U1.13 (GPIO9)
/GPIO10: U1.14 (GPIO10)
/GPIO11: U1.15 (GPIO11)
/GPIO12: U1.16 (GPIO12)
/GPIO13: U1.17 (GPIO13)
/GPIO14: U1.18 (GPIO14)
/GPIO15: U1.19 (GPIO15)
/GPIO16: U1.27 (GPIO16)
/GPIO17: U1.28 (GPIO17)
/GPIO18: J4.4 (ID), TP5.1, U1.29 (GPIO18)
/GPIO19: J1.14, TP4.1, U1.31 (GPIO19)
/GPIO20: J1.25, TP2.1, U1.32 (GPIO20)
/GPIO21: J1.24, TP3.1, U1.33 (GPIO21)
/GPIO22: U1.34 (GPIO22)
/GPIO23: U1.35 (GPIO23)
/GPIO24: U1.36 (GPIO24)
/GPIO25: U1.37 (GPIO25)
/GPIO26_ADC0: U1.40 (GPIO26_ADC0)
/GPIO27_ADC1: U1.41 (GPIO27_ADC1)
/GPIO28_ADC2: U1.42 (GPIO28_ADC2)
/GPIO29_ADC3: U1.43 (GPIO29_ADC3)
/HPD: J1.17, J3.17
/MCU_USB_DN: R7.2, U1.51 (USB_DM)
/MCU_USB_DP: R8.2, U1.52 (USB_DP)
/QSPI_SCLK: U1.56 (QSPI_SCLK)
/QSPI_SD0: U1.57 (QSPI_SD0)
/QSPI_SD1: U1.59 (QSPI_SD1)
/QSPI_SD2: U1.58 (QSPI_SD2)
/QSPI_SD3: U1.55 (QSPI_SD3)
/QSPI_SS: R6.1, U1.60 (QSPI_SS)
/RUN: JP2.2 (B), U1.26 (RUN)
/SWCLK: U1.24 (SWCLK)
/SWD: U1.25 (SWD)
/TEST: J3.14, TP1.1
/TP_D+: J3.32, R4.1
/TP_D-: J3.31, R10.1
/UDN: J4.2 (D-), R7.1
/UDP: J4.3 (D+), R8.1
/VREG_AVDD: C3.1, R5.1, U1.46 (VREG_AVDD)
/VREG_LX: L1.2, U1.48 (VREG_LX)
/VTSP: J3.34, J3.35, JP1.2 (C)
/XIN: R9.1, U1.21 (XIN)
/XOUT: U1.22 (XOUT)
/~BOOT: R6.2, SW1.A
GND: C1.2, C3.2, C4.2, C5.2, C6.2, C8.2, C11.2, C12.2, C13.2, C14.2, C15.2, C16.2, C17.2, C18.2, J1.2, J1.5, J1.8, J1.11, J1.15, J1.16, J1.MP (MountPin), J3.2, J3.5, J3.8, J3.11, J3.15, J3.16, J3.33, J3.MP (MountPin), J4.5 (GND), J4.6 (Shield), JP2.1 (A), SW1.C, U1.47 (VREG_PGND), U1.61 (GND), Y1.2
unnamed: R9.2, Y1.3
VBUS: J4.1 (VBUS), JP1.3 (B)

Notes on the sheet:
POWER
Special pins in eDP: 1, 24, 25, 30: NC/Reserved 14: Test 17: HPD NOTE USAGE OF pins 24/25 and 14 for I2C
USB Connector
TODO: -Add pullups for I2C -Add 3.3V and GND test points -Add "buffer full" signal and an optional LED
FPC Connectors
MCU
This oscillator with 27 ohm works ok
DECOUPLING
VTSP can work at 3.3V on some panels specified for 5V

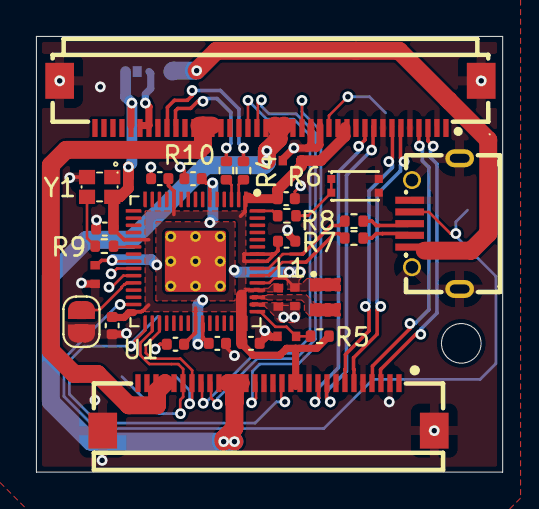
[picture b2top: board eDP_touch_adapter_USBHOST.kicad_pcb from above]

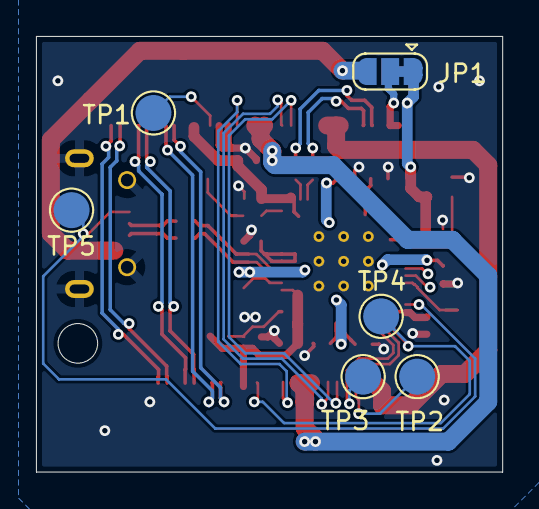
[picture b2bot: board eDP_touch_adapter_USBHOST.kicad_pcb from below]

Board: 2 copper layers, 25.9 x 24.2 mm, 36 parts (6 on the bottom side), 36 nets.

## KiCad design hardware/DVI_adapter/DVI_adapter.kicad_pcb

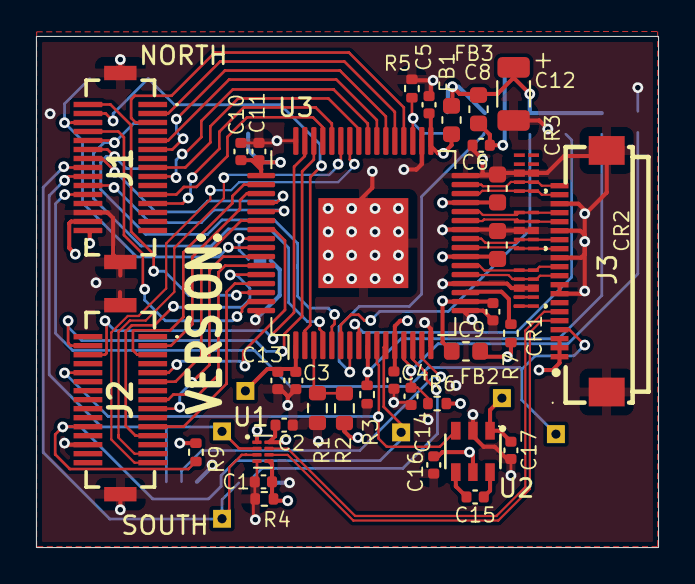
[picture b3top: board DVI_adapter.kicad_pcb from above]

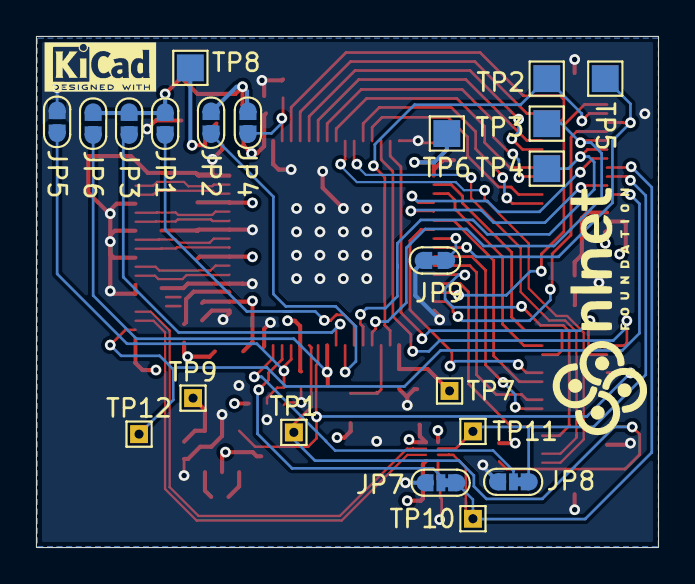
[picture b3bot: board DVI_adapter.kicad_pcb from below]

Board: 4 copper layers, 34.6 x 28.4 mm, 58 parts (21 on the bottom side), 65 nets.

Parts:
C1, C2, C3, C4, C5, C14: 0.1uF; C_0402_1005Metric
C6, C7: 0.01uF; C_0603_1608Metric
C8, C11, C13, C15, C16, C17: 2.2uF; C_0402_1005Metric
C9, C10: 0.01uF; C_0402_1005Metric
C12: 22uF; C_1206_3216Metric
CR1, CR2, CR3: ESD7004MUTAG; UDFN10_517BB_ONS-L
FB1, FB2, FB3: SZ1608K601TF; L_0603_1608Metric
J1, J2: DF12NB(3.0)-30DS-0.5V(51); DF12NB3030DP05V51
J3: FPC Cable connector 1x20; FPC-SMD_XUNPU_FPC-0.5FX-20PWBH15
JP1: JMP_DK3; SolderJumper-2_Open_RoundedPad_2.254x0.95mm
JP2: JMP_DK2; SolderJumper-2_Open_RoundedPad_2.254x0.95mm
JP3: JMP_DK1; SolderJumper-2_Open_RoundedPad_2.254x0.95mm
JP4: JMP_DKEN; SolderJumper-2_Open_RoundedPad_2.254x0.95mm
JP5: JMP_ISEL; SolderJumper-2_Open_RoundedPad_2.254x0.95mm
JP6: JMP_EDGE; SolderJumper-2_Open_RoundedPad_2.254x0.95mm
JP7: JMP_SDA; SolderJumper-3_Bridged_RoundedPad2.71x0.95mm
JP8: JMP_SCK; SolderJumper-3_Bridged_RoundedPad2.71x0.95mm
JP9: JMP_CKn; SolderJumper-2_Closed_RoundedPad_2.254x0.95mm
R1: 8.06K 1%; R_0603_1608Metric
R2: 8.45K 1%; R_0603_1608Metric
R3, R5, R6: 10K; R_0402_1005Metric
R4: DNP (10K); R_0402_1005Metric
R7: 510; R_0402_1005Metric
R9: 4.7k; R_0402_1005Metric
TP1: TP_MSEN; TestPoint_THTPad_1.0x1.0mm_Drill0.5mm
TP2: TP_DE; TestPoint_Pad_1.5x1.5mm
TP3: TP_HS; TestPoint_Pad_1.5x1.5mm
TP4: TP_VS; TestPoint_Pad_1.5x1.5mm
TP5: TP_PCLK; TestPoint_Pad_1.5x1.5mm
TP6: TP_PVDD; TestPoint_Pad_1.5x1.5mm
TP7: TP_DVDD; TestPoint_THTPad_1.0x1.0mm_Drill0.5mm
TP8: TP_TVDD; TestPoint_Pad_1.5x1.5mm
TP9: TP_VDVI; TestPoint_THTPad_1.0x1.0mm_Drill0.5mm
TP10: TP_SDA; TestPoint_THTPad_1.0x1.0mm_Drill0.5mm
TP11: TP_SCK; TestPoint_THTPad_1.0x1.0mm_Drill0.5mm
TP12: TP_HPD; TestPoint_THTPad_1.0x1.0mm_Drill0.5mm
U1: TXS0102DQE; X2SON-8_1.4x1mm_P0.35mm
U2: HE9009M6R; SOT-23-6_L2.9-W1.7-P0.95-LS2.8-BL
U3: TFP410; LQFP-64-1EP_10x10mm_P0.5mm_EP5x5mm

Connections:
+3V3: C12.1, C16.1, FB1.1, FB2.1, FB3.1, J1.30 (29), JP1.1 (A), JP2.1 (A), JP3.1 (A), JP4.1 (A), JP6.1 (A), R6.2, R7.2, U2.5 (VIN)
/TX0+: CR2.2, CR2.9, J3.7, U3.25 (TX0+)
/TX0-: CR2.1, CR2.10, J3.8, U3.24 (TX0-)
/TX1+: CR2.5, CR2.6, J3.4, U3.28 (TX1+)
/TX1-: CR2.4, CR2.7, J3.5, U3.27 (TX1-)
/TX2+: CR3.2, CR3.9, J3.1, U3.31 (TX2+)
/TX2-: CR3.1, CR3.10, J3.2, U3.30 (TX2-)
/TXC+: CR1.5, CR1.6, J3.10, U3.22 (TXC+)
/TXC-: CR1.4, CR1.7, J3.11, U3.21 (TXC-)
B0: J1.8 (7), U3.63 (DATA0)
B1: J1.2 (1), U3.62 (DATA1)
B2: J2.21 (22), U3.61 (DATA2)
B3: J2.23 (24), U3.60 (DATA3)
B4: J2.15 (16), U3.59 (DATA4)
B5: J2.17 (18), U3.58 (DATA5)
B6: J2.9 (10), U3.55 (DATA6)
B7: J2.11 (12), U3.54 (DATA7)
DVDD: C3.1, C4.1, C5.1, C13.1, FB1.2, TP7.1, U3.1 (DVDD), U3.12 (DVDD), U3.33 (DVDD)
G0: J1.20 (19), U3.53 (DATA8)
G1: J1.14 (13), U3.52 (DATA9)
G2: J2.3 (4), U3.51 (DATA10)
G3: J2.5 (6), U3.50 (DATA11)
G4: J2.6 (5), U3.47 (DATA12)
G5: J2.4 (3), U3.46 (DATA13)
G6: J1.21 (22), U3.45 (DATA14)
G7: J1.23 (24), U3.44 (DATA15)
GND: C1.2, C2.2, C3.2, C4.2, C5.2, C6.2, C7.2, C8.2, C9.2, C10.2, C11.2, C12.2, C13.2, C14.1, C16.2, C17.2, CR1.3, CR1.8, CR2.3, CR2.8, CR3.3, CR3.8, J1.26 (25), J1.MP1, J1.MP2, J2.26 (25), J2.MP1, J2.MP2, J3.0, J3.3, J3.6, J3.9, J3.12, J3.13, JP5.1 (A), JP7.3 (B), JP8.3 (B), JP9.1 (A), R1.1, R3.2, R4.2, R5.2, U1.4 (GND), U2.2 (GND), U3.16 (DGND), U3.17 (PGND), U3.20 (TGND), U3.26 (TGND), U3.32 (TGND), U3.34 (RESERVED), U3.48 (DGND), U3.64 (DGND), U3.65 (middle_pad)
HPD: J1.22 (21), J3.17, TP12.1
HPD2: J2.22 (21), R9.2, TP1.1, U3.11 (MSEN)
LCD_DE: J1.4 (3), TP2.1, U3.2 (DE)
LCD_HSYNC: J1.10 (9), TP3.1, U3.4 (HSYNC)
LCD_VSYNC: J1.12 (11), TP4.1, U3.5 (YSYNC)
unnamed: CR1.1, CR1.10
unnamed: CR1.2, CR1.9
unnamed: JP1.2 (B), U3.6 (CTL3)
unnamed: JP2.2 (B), U3.7 (CTL2)
unnamed: JP3.2 (B), U3.8 (CTL1)
unnamed: JP4.2 (B), R5.1, U3.35 (DKEN)
unnamed: C14.2, JP5.2 (B), R6.1, U3.13 (ISEL)
unnamed: JP6.2 (B), R3.1, U3.9 (EDGE/HTPLG)
unnamed: JP7.2 (C), U3.14 (DSEL)
unnamed: JP8.2 (C), U3.15 (BSEL)
unnamed: JP9.2 (B), U3.56 (IDCK-)
unnamed: C15.2, U2.4 (CN)
unnamed: C15.1, U2.6 (CP)
unnamed: R7.1, U3.19 (TFADJ)
unnamed: R1.2, R2.1, U3.3 (Vref)
PCLK: J1.6 (5), TP5.1, U3.57 (IDCK+)
PSEL: J2.10 (9), U2.3 (EN), U3.10 (PD)
PVDD: C9.1, C10.1, C11.1, FB2.2, TP6.1, U3.18 (PVDD), U3.49 (PVDD)
R0: J2.27 (28), U3.43 (DATA16)
R1: J2.29 (30), U3.42 (DATA17)
R2: J1.15 (16), U3.41 (DATA18)
R3: J1.17 (18), U3.40 (DATA19)
R4: J1.9 (10), U3.39 (DATA20)
R5: J1.11 (12), U3.38 (DATA21)
R6: J1.3 (4), U3.37 (DATA22)
R7: J1.5 (6), U3.36 (DATA23)
SCK: J1.18 (17), JP8.1 (A), TP11.1, U1.2 (A1)
SCK_SHIFTED: J3.15, U1.7 (B1)
SDA: J1.16 (15), JP7.1 (A), TP10.1, U1.3 (A2)
SDA_SHIFTED: J3.16, U1.6 (B2)
TVDD: C6.1, C7.1, C8.1, FB3.2, TP8.1, U3.23 (TVDD), U3.29 (TVDD)
VCC3V3: C1.1, J1.28 (27), R2.2, R4.1, R9.1, U1.1 (VCCA), U1.5 (OE)
V_DVI: C2.1, C17.1, J3.18, J3.19, J3.20, TP9.1, U1.8 (VCCB), U2.1 (VOUT)

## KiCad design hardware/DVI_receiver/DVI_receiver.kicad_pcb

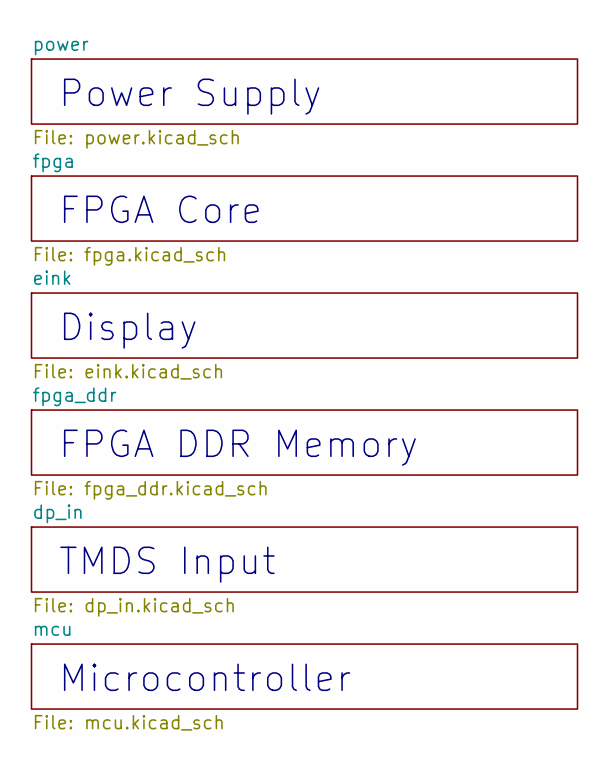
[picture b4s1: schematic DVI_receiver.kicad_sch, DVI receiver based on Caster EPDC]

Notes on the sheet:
FPGA DDR Memory
Power Supply
Microcontroller
Display
FPGA Core
TMDS Input

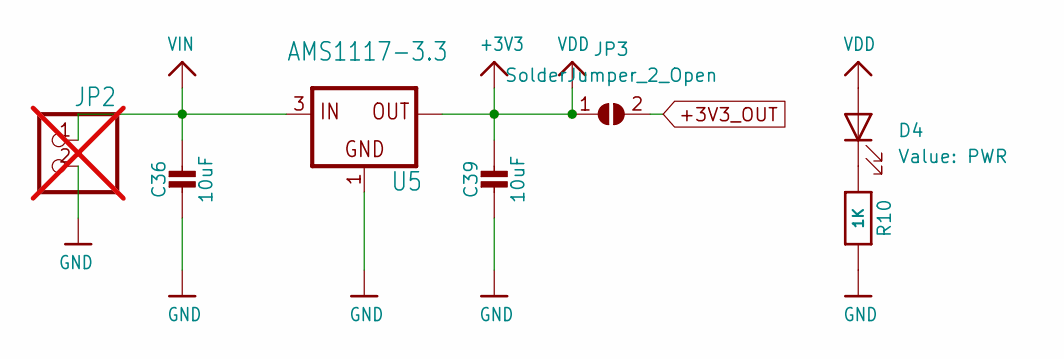
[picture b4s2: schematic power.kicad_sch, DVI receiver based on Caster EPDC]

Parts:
C36, C39: 10uF; C_1206_3216Metric; MPN CL31A106KBHNNNE
D4: PWR; LED_0603_1608Metric
JP2: HEADER-1X2ROUND; PinHeader_1x02_P2.54mm_Vertical; not fitted
JP3: SolderJumper_2_Open; SolderJumper-2_P1.3mm_Open_RoundedPad1.0x1.5mm
R10: 1K; R_0402_1005Metric
U5: AMS1117-3.3; SOT-223; MPN AMS1117-3.3

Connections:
+3V3_OUT: JP3.2 (B); also elsewhere on the board
GND: C36.2, C39.2, JP2.2, R10.2, U5.1 (GND); also elsewhere on the board
unnamed: D4.1 (K), R10.1
VIN: C36.1, JP2.1, U5.3 (IN); also elsewhere on the board
VIO: C39.1, D4.2 (A), JP3.1 (A), U5.2 (OUT), U5.4 (OUT); also elsewhere on the board

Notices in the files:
hardware/CPU_board/CPU_board.kicad_sch:
(C) 2023-2024 Victor Suarez Rovere
hardware/DVI_adapter/DVI_adapter.kicad_pcb:
Copyright (C) Victor Suarez Rovere
License:  CERN OHL-S
hardware/README.md:
The design is done with the open-source EDA tool [Kicad](https://kicad.org), the source files are [here](./DVI_adapter) (adapter) and [here](./DVI_connector_board) (connector), licensed under a **CERN open-source hardware** license.
hardware/Spartan6_board/dp_in.kicad_sch:
(C) 2025-2026 Victor Suarez Rovere
Copyright 2023 Modos / Engineer: Wenting Zhang
